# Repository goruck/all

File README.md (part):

*NEW - ALL now supports Raspberry Pi 3 running Raspbian Buster + PREEMPT-RT patched kernel 4.19.59-rt23-v7+.*

# What is Alexa Lambda Linux (ALL) Project?
* ALL is an end-to-end HW/SW reference design created to enable quick prototyping and realization of the control and monitoring of things using Amazon’s Alexa.
* ALL includes Amazon’s Alexa Skills Kit and Lambda running in the cloud as well as a local server based on real-time Linux running on the Raspberry Pi.
* ALL also includes machine learning capabilities at the edge. 
* A voice-controlled home security system was built from ALL as an early proof of concept.
* ALL was introduced in late 2015 at https://github.com/goruck/all.

# ALL System Block Diagram

# ALL Overview
Using voice to interface with devices and services around the home enables a rich and intuitive experience as shown by Amazon's huge successes with FireTV and Echo. However, with the exception of a few 3rd party point solutions such as WeMo, the voice user interface is generally not available in the home. One reason for this is the difficulty and unfamiliarity of the technologies required to enable voice control.

Alexa Lambda Linux (ALL) was developed to help accelerate this learning curve. ALL is a HW/SW reference design meant to enable quick prototyping and realization of the control and monitoring of things using Amazon's Alexa. A voice-controlled home security system was first built from the reference design as proof of concept which was later extended to support machine learning. 

The README below describes the system, the main components, its design, and implementation. It is expected that people will find it useful in creating voice user interfaces of their own using Alexa, Lambda, Linux, and the Raspberry Pi.

Feature | Benefit
------------ | -------------
Integrated with Lambda and ASK | Quick bring-up of new voice controls
Real-time Linux / user space app dev model | Low effort to control fast real-world events
Raspberry PI, open source, AWS services | Low cost and quick deployment
End to end SSL/TLS integration | Customer data security

# Table of Contents
1. [Requirements and System Architecture](https://github.com/goruck/all#requirements-and-system-architecture)
2. [Design and Implementation of the Main Components](https://github.com/goruck/all#design-and-implementation-of-the-components)
   1. [Alexa Intent Schema / Utterance database](https://github.com/goruck/all#alexa-intent-schema--utterance-database)
   2. [AWS Lambda function](https://github.com/goruck/all#aws-lambda-function)
   3. [Raspberry Pi Controller / Server](https://github.com/goruck/all#raspberry-pi-controller--server)
   4. [Keybus to GPIO Interface Unit](https://github.com/goruck/all#keybus-to-gpio-interface-unit)
3. [Machine Learning with ALL](https://github.com/goruck/all/blob/master/README.md#machine-learning-with-all)
   1. [Background Information](https://github.com/goruck/all/blob/master/README.md#background-information)
   2. [Problem Definition](https://github.com/goruck/all/blob/master/README.md#problem-definition)
   3. [Data Preparation](https://github.com/goruck/all/blob/master/README.md#data-preparation)
   4. [Data Analysis](https://github.com/goruck/all/blob/master/README.md#data-analysis)
   5. [Algorithm Evaluation](https://github.com/goruck/all/blob/master/README.md#algorithm-evaluation)
   6. [Implementation](https://github.com/goruck/all/blob/master/README.md#implementation)
   7. [Results](https://github.com/goruck/all/blob/master/README.md#results)
4. [Development and Test environment](https://github.com/goruck/all#development-and-test-environment)
5. [Overall Hardware Design and Considerations](https://github.com/goruck/all#overall-hardware-design-and-considerations)
6. [Bill of Materials and Service Cost Considerations](https://github.com/goruck/all#bill-of-materials-and-service-cost-considerations)
7. [Licensing](https://github.com/goruck/all/blob/master/README.md#licensing)
8. [Contact Information](https://github.com/goruck/all/blob/master/README.md#contact-information)
9. [Appendix](https://github.com/goruck/all#appendix)

# Requirements and System Architecture
Please see below the high-level requirements that the project had to meet.

* Low cost
* Extensible / reusable with low effort
* Secure
* Enable fast prototyping and development
* Include at least one real world application

Meeting these requirements would prove this project useful to a very wide variety of voice interface applications. In addition, implementing a non-trivial "real-world" application would show that the design is robust and capable. Hence the last requirement, which drove the implementation of a voice user interface on a standard home security system, the DSC Power832.

The system needs both cloud and (home-side) device components. Amazon's Alexa was selected as the cloud speech service and Amazon Web Services' Lambda was selected to handle the cloud side processing required to interface between Alexa and the home-side devices. Alexa is a good choice given that its already integrated with Lambda and has a variety of voice endpoints including Echo and FireTV and it costs nothing to develop voice applications via the [Alexa Skills Kit](https://developer.amazon.com/public/solutions/alexa/alexa-skills-kit). [Lambda](https://aws.amazon.com/lambda/) is ideal for quickly handling bursty processing loads, which is exactly what is needed to control things with voice. It also has a free tier under a certain amount of processing and above that its still very inexpensive. So, Alexa and Lambda are reasonable cloud choices given the requirements above.

The [Raspberry Pi 2](https://www.raspberrypi.org/blog/raspberry-pi-2-on-sale/) was designated as the platform to develop the home-side device components( All also supports the Raspberry Pi 3.) The platform has a powerful CPU, plenty RAM, a wide variety of physical interfaces, has support for many OSs, and is inexpensive. It is possible to use an even more inexpensive platform like [Arduino](https://www.arduino.cc/) but given its lower capabilities vis-a-vis the Raspberry PI this would limit the types of home-side applications that could be developed. For example, use of GNU/Linux is desirable in this project for extensibility and rapid development reasons. Arduino isn't really capable of running Linux but the Pi is. The downside of using the Pi plus a high-level OS like vanilla Linux is that the system cannot process quickly changing events (i.e., in "real-time"). On the other hand, the Arduino running bare metal code is a very capable real-time machine. To be as extensible as possible, the system needs to support the development of real-time voice controlled applications and without complex device side architectures like using an Arduino to handle the fast events connected to a Pi to handle the complex events. Such an architecture would be inconsistent with the project requirements. Therefore [real-time Linux](https://wiki.linuxfoundation.org/realtime/start) was chosen as the OS on the Pi. However, this comes with the downsides of using a non-standard kernel and real-time programming is less straightforward than standard application development in Linux userspace.

In the reference design, the Pi's GPIOs are the primary physical interface to the devices around the home that are enabled with a voice UI. This allows maximum interface flexibility, and with using real-time Linux, the GPIO interface runs fast. The reference design enables GPIO reads and writes with less than 60 us latency, vanilla Linux at best can do about 20 ms. Of course, all the other physical interfaces (SPI, I2C, etc.) on the Pi are accessible in the reference design though the normal Linux methods.

The requirements and the analysis above drove a system architecture with the following components.

* Alexa Skills developed using the Alexa Skills Kit
* An AWS Lambda function in Node.js to handle the intent triggers from Alexa and send it back responses from the home device 
* A home device built on Raspberry PI running real-time Linux with a server application developed in C running in userspace
* A hardware interface unit that handled the translation of the electrical signals between the Pi and the security system
* The DSC Power832 security system connected via its Keybus interface to the Pi's GPIOs via the interface unit.

Note that although the development of the architecture described above appears very waterfall-ish, the reality is that it took many iterations of architecture / design / test to arrive at the final system solution.

# Design and Implementation of the Components

## Alexa Skills
Creating Alexa Skills (which are essentially voice apps) is done by using the Alexa Skills Kit. An Amazon applications developer account is required to get access to the [Alexa Skills Kit (ASK)](https://developer.amazon.com/public/solutions/alexa/alexa-skills-kit), one can be created one at https://developer.amazon.com/appsandservices. There's a [getting started guide](https://developer.amazon.com/appsandservices/solutions/alexa/alexa-skills-kit/getting-started-guide) on the ASK site on how to create a new skill. The skill developed to control the alarm panel, named *panel*, used the example skill *color* as a starting point. Amazon makes the creation of a skill relatively easy but careful thinking through the voice interaction is required. The *panel* skill uses a mental model of attaching a voice command to every button on the alarm's keypad and an extra command to give the status of the system. The alarm system status is the state of the lights on the keypad (e.g., armed, bypass, etc). Four-digit code input is also supported, which is useful for a PIN. The Amazon skill development tool takes you through the following steps in creating the skill:

1. Skill Information - Invocation Name, Version, and Service Endpoint (the Lambda ARN in this project)
2. Interaction Model - Intent Schema, Custom Slot Types, and Sample Utterances
3. Test
4. Description
5. Publishing Information (the *panel* skill is not currently published)

The creation of the *panel* skill required inputting of an [Intent Schema](https://github.com/goruck/all/blob/master/ask/IntentSchema.txt) (which defines the voice interaction model), [sample utterances](https://github.com/goruck/all/blob/master/ask/SampleUtterances.txt), and [custom slot definitions](https://github.com/goruck/all/blob/master/ask/CustomSlotTypes.txt) which are essentially elaborations of the values of parameters used in the Intent Schema. The ASK service will generate a voice model from these inputs. 

The table below shows some of the mapping between example user requests and the sample utterance syntax used in the interaction model. 

Example User Request | Sample Utterance
---------------------|------------------
“Alexa, ask Panel for its status” | WhatsMyStatusIntent its status
“Alexa, ask Panel about its status” |WhatsMyStatusIntent its status
“Alexa, ask Panel for the status” | WhatsMyStatusIntent the status
“Alexa, ask Panel about the status” | WhatsMyStatusIntent the status
“Alexa, ask Panel for status” | WhatsMyStatusIntent status
“Alexa, ask Panel about status” | WhatsMyStatusIntent status
“Alexa, ask Panel for the status” | WhatsMyStatusIntent the status
“Alexa, ask Panel about the status” | WhatsMyStatusIntent the status
“Alexa, ask Panel what is the status” | WhatsMyStatusIntent what is the status
“Alexa, ask Panel what the status is” | WhatsMyStatusIntent what the status is
“Alexa, ask Panel what's the status” | WhatsMyStatusIntent what's the status
“Alexa, ask Panel to give me the status” | WhatsMyStatusIntent give me the status
“Alexa, ask Panel to give me its status” | WhatsMyStatusIntent give me its status
“Alexa, ask Panel to tell me the status” | WhatsMyStatusIntent tell me the status
“Alexa, ask Panel to tell me its status” | WhatsMyStatusIntent tell me its status
"Alexa, ask Panel for key pound" | MyNumIsIntent key {Keys}
"Alexa, ask Panel for button star" | MyNumIsIntent button {Keys}
"Alexa, ask Panel for key pad button 0" | MyNumIsIntent key pad button {Keys}
"Alexa, ask Panel for 8" | MyNumIsIntent {Keys}
"Alexa, ask Panel for pin 1234" | MyCodeIsIntent pin {Code}
"Alexa, ask Panel for code 5678" | MyCodeIsIntent code {Code}
"Alexa, ask Panel for 4545" | MyCodeIsIntent {Code}

The "LIST_OF_KEYS" slot enables the intent "MyNumIsIntent" to activate when Alexa hears the name of the buttons on the keypad defined by the slot. The intent "WhatsMyStatusIntent" activates when Alexa hears any of the status related utterances listed above. The intent "MyCodeIsIntent" activates when Alexa hears a 4-digit code. When the intents activate, they cause the service endpoint Lambda function to run and perform specific processing depending on the user intent.

The skill is invoked by saying to Alexa "ask panel" or "tell panel".

## AWS Lambda function
An Amazon Web Services account is needed to use Lambda, one can be created at at https://aws.amazon.com/. Like all AWS products, there is good [documentation](https://aws.amazon.com/lambda/) available on the AWS site that should be read to come up to speed, if not already familiar. Still it can be challenging to use the product, if unfamiliar with javascript, Node, and asynchronous programming which are all essential to using Lambda. Several books and articles including [*Sams Teach Yourself Node.js in 24 Hours*](http://smile.amazon.com/dp/0672335956) by Ornbo, [*JavaScript: The Good Parts*](http://smile.amazon.com/dp/0596517742) by Crockford, and [*Asynchronous programming and continuation-passing style in JavaScript*](http://www.2ality.com/2012/06/continuation-passing-style.html) by Rauschmayer can help to accelerate the learning curve. Lambda and Node.js is very well-suited to scale cloud side processing associated with applications like voice control, given that Lambda was designed to handle bursty applications and the non-blocking I/O benefits of Node.js.

The *color* skill and Lambda function example provided by ASK was used as a template to create the Lambda function for *panel*. Since the Lambda function needed to talk to a remote Raspberry Pi server, that functionality was added as well as modifying the logic and speech responses to suit the alarm application. The Lambda code uses the Node.js tls method to open, read, and write a TCP socket that connects to the remote Pi server which sends commands to and reads status from the panel. The tls method provides both authentication and encryption between the Lambda client and the Pi server. One of the biggest challenges in this development is the placement of the  callbacks that returned responses back to Alexa due to the async nature of Node.js. The rest of the Lambda function development was straightforward. 

The Lambda code is divided up into three parts, [all.js](https://github.com/goruck/all/blob/master/lambda/all.js) contains most of the functions required to process the speech intents from the Alexa service and interface to the local Pi in a client - server model. However, some Lambda code requires it to be released under the Amazon License which is in the [amzn](https://github.com/goruck/all/tree/master/lambda/amzn) directory. Lastly, the Lambda code common to all.js and the code in the amzn directory is in [shared.js](https://github.com/goruck/all/blob/master/lambda/shared.js).

## Raspberry Pi Controller / Server

### Real-time Linux
The Linux disto on the Pi is based on Debian 10 "Buster" with a custom built [Raspberry Pi Linux 4.19.y kernel](https://github.com/raspberrypi/linux/tree/rpi-4.19.y-rt) patched with rt-patch and configured as a fully preemptible kernel. The kernel was cross-compiled on a Linux host using the official [Raspberry Pi instructions](https://www.raspberrypi.org/documentation/linux/kernel/building.md) and [LeMaRiva's excellent HOWTO](https://lemariva.com/blog/2019/09/raspberry-pi-4b-preempt-rt-kernel-419y-performance-test) as guides. Also the wiki [real-time Linux](https://wiki.linuxfoundation.org/realtime/start) is an invaluable source of information on the rt-patch and how to write real-time code.

The latency of the patched kernel was measured using [Cyclictest](https://wiki.linuxfoundation.org/realtime/documentation/howto/tools/cyclictest/start) which showed a worse case latency of less than 135 us. So, that seemed to indicate that applications could reliably respond to events up to about 7.4 kHz which is sufficient for this application which needs to respond to events at a 1 KHz rate (see below).

The distribution of the latency on the patched kernel as measure by Cyclictest is shown below.

### Controller / Server Application
The application code on the Pi emulates a DSC keypad controller running in the Linux system's userspace. The application code in its entirety can be found [here](https://github.com/goruck/all/blob/master/rpi/kprw-server.c), this section captures important design considerations that are not obvious from the code itself or the comments therein.

The DSC system is closed and proprietary and besides the installation and programming information in the DSC manuals and what hackers have managed to figured out and posted on the Internet and GitHub, there isn't much information available about the protocol it uses to communicate with its keypads. Also, much of of what is on the Internet relies on using an IP interface bridge like this [one](http://www.eyezon.com/?page_id=176) from Eyezon. A bridge like this instead of the code on the Raspberry Pi could have been used in this project but that would have made the reference design much less generic (and much less fun to develop). A lot of useful information on how to hack the DSC system can be found in the [Arduino-Keybus](https://github.com/emcniece/Arduino-Keybus) GitHub repo, but this project uses an Arduino which was ruled out (see above) and it was read-only. Still, it is very educational. Although these sources helped, a lot of reverse engineering was required to figure out the protocol used on the DSC Keybus. The reverse engineering mainly consisted of using an early version of the application code to examine the bits sent from the panel to the keypads and the keypads to the panel in response to keypad button presses and other events, like motion and door / window openings and closings. It was determined that the first two bytes of each message indicates its type, followed by a variable number of data bits including error protection. For example a message with its first two bytes equal to 0x05 is telling the keypad to illuminate specific status LEDs, such as BYPASS, READY, etc and a message type equal to 0xFF indicates keypad to panel data is being sent. See the *decode()* function in the application code for details regarding the various message types and their contents.

The application code consists of three main parts:

* A thread called *panel_io()* that handles the bit-level processing needed to assemble messages from the keybus serial data
* A thread called *msg_io()* that handles the message-level output processing
* A server called *panserv()* running in the main thread that communicates with an external client for commands and status

The application code directly accesses the GPIO's registers for the fastest possible reads and writes. The direct access code is based on [this](http://elinux.org/RPi_GPIO_Code_Samples#Direct_register_access) information from the Embedded Linux Wiki at elinux.org. The function *setup_io()* in the application code sets up a memory regions to access the GPIOs. The information in the Broadcom BCM2835/6 ARM Peripherals document is very useful to understand how to safely access the Pi's processor peripherals. It is [here](http://elinux.org/RPi_Documentation) on the Embedded Linux Wiki site.

Inter-thread communication is handled safely via read and write FIFOs without any synchronization (e.g., using a mutext). Its not desirable to use conventional thread synchronization methods since they would block the *panel_io()* thread. There is no way (to my knowledge) to tell the panel not to send data on the keybus, so if *panel_io()* was blocked by another thread accessing a shared FIFO, the application code would drop messages. A good solution to this problem was found in the article [Creating a Thread Safe Producer Consumer Queue in C++ Without Using Locks](http://blogs.msmvps.com/vandooren/2007/01/05/creating-a-thread-safe-producer-consumer-queue-in-c-without-using-locks/) by Vandooren, which is what was implemented with a few modifications.

Running code under real-time Linux requires a few special considerations. Again, the [real-time Linux](https://rt.wiki.kernel.org/index.php/Main_Page) wiki was used extensively to guide the efforts in this regard. The excellent book [The Linux Programming Interface](http://man7.org/tlpi/) by Kerrisk also was very helpful to understand more deeply how the Linux kernel schedules tasks. There are three things needed to be set by a task in order to provide deterministic real time behavior:

1. Setting a real time scheduling policy and priority by use of the *sched_setscheduler()* system call and its pthread cousins. Note that *panel_io()*, *message_io()*, and *main()* were all given the same scheduling policy (SCHED_FIFO) but *panel_io()* has a higher priority than *message_io()* and *main()*. This was done to ensure that the bit-level processing would have enough time to complete. 
2. Locking memory so that page faults caused by virtual memory will not undermine deterministic behavior. This is done with the *mlockall()* system call. 
3. Pre-faulting the stack, so that a future stack fault will not undermine deterministic behavior. This is done by simply accessing each element of the program's stack by use of the *memset()* system call. 

Extensive use of the *clock_nanosleep()* function from librt is used in the code. For example, its use is shown in the *panel_io()* thread where it awakens the thread every INTERVAL (10 us) to read and write to the GPIOs driving the keybus clock and data lines (via the interface unit). The thread contains logic to detect the start of word marker, to detect high and low clock periods, and to control precisely when the GPIOs are read and written. The below taken from *panel_io()* causes the thread to wait for valid data before reading the GPIO.

```c
t.tv_nsec += KSAMPLE_OFFSET;
tnorm(&t);
clock_nanosleep(CLOCK_MONOTONIC, TIMER_ABSTIME, &t, NULL); // wait KSAMPLE_OFFSET for valid data
wordkr_temp = (GET_GPIO(PI_DATA_IN) == PI_DATA_HI) ? '0' : '1'; // invert
```

Even though the *panel_io()* is given higher priority than the other two threads, other critical threads in the Linux kernel must have higher still priority for the overall system to function. Therefore it is possible that a higher priority kernel task could preempt *panel_io()* and cause it to drop bits. The real-time Linux wiki suggests this solution:

*"In general, I/O is dangerous to keep in an RT code path. This is due to the nature of most filesystems and the fact that I/O devices will have to abide to the laws of physics (mechanical movement, voltage adjustments, <whatever an I/O device does to retrieve the magic bits from cold storage>). For this reason, if you have to access I/O in an RT-application, make sure to wrap it securely in a dedicated thread running on a disjoint CPU from the RT-application."* 

Based on this, the *panel_io()* thread was locked to its own CPU and the other threads are locked to the other three CPUs (its really great to have four CPUs at one's disposal). The application code sets the thread CPU affinity as shown below. 

```c
// CPU(s) for main, predict and message i/o threads
  CPU_ZERO(&cpuset_mio);
  CPU_SET(1, &cpuset_mio);
  CPU_SET(2, &cpuset_mio);
  CPU_SET(3, &cpuset_mio);
  CPU_ZERO(&cpuset_main);
  CPU_SET(1, &cpuset_main);
  CPU_SET(2, &cpuset_main);
  CPU_SET(3, &cpuset_main);
  // CPU(s) for panel i/o thread
  CPU_ZERO(&cpuset_pio);
  CPU_SET(0, &cpuset_pio);
```

With the threads pinning to the CPUs in this way and with the priority of *panel_io()* being greater than the other two threads in the application code (but not greater than the kernel's critical threads), the system exhibits robust real-time performance.

The server uses openSSL for authentication and encryption. For development and test purposes self-signed certificates are used. The cert and key pairs are generated with the following commands.

```bash
# Step 1. Generate ca private key
$ openssl genrsa -out /home/pi/certs/ca/ca.key 4096
# Step 2. Create self-signed ca cert, COMMON_NAME="My CA"
$ openssl req -new -x509 -days 365 -key /home/pi/certs/ca/ca.key -out /home/pi/certs/ca/ca.crt -sha256
# 
# Step 3. Create client private key
$ openssl genrsa -out /home/pi/certs/client/client.key 2048
# Step 4. Create client cert signing request, COMMON_NAME="Client 1"
$ openssl req -new -key /home/pi/certs/client/client.key -out /home/pi/certs/client/client.csr -sha256
# Step 5. Create signed client cert
$ openssl x509 -req -days 365 -in /home/pi/certs/client/client.csr -CA /home/pi/certs/ca/ca.crt -CAkey /home/pi/certs/ca/ca.key -set_serial 01 \
-out /home/pi/certs/client/client.crt -sha256
# 
# Step 6. Create server private key
$ openssl genrsa -out /home/pi/certs/server/server.key 2048
# Step 7. Create server cert signing request, COMMON_NAME="localhost"
$ openssl req -new -key /home/pi/certs/server/server.key -out /home/pi/certs/server/server.csr -sha256
# Step 8. Create signed server cert, where "key.ext" contains "subjectAltName = IP:xxx.xxx.xxx.xxx"
$ openssl x509 -req -days 365 -in /home/pi/certs/server/server.csr -CA /home/pi/certs/ca/ca.crt -CAkey /home/pi/certs/ca/ca.key -set_serial 02 \
-out /home/pi/certs/server/server.crt -sha256 -extfile /home/pi/certs/server/key.ext
# 
# Step 9. Copy client key pair and CA certificate to Lambda
$ cp /home/pi/certs/client/client.crt /home/pi/all/lambda
$ cp /home/pi/certs/client/client.key /home/pi/all/lambda
$ cp /home/pi/certs/ca/ca.crt /home/pi/all/lambda
```

Note: replace the X's in key.ext with the IP address or hostname of your server.

Production code should use certificates signed by a real CA. The server also uses TCP Wrapper daemon for secure access. TCP Wrapper uses the *hosts_ctl()* system call from libwrap library to limit client access via the rules defined in /etc/host.deny and /etc/host.allow files. The rules are set so that only clients with local IP addresses and AWS IP addresses are allowed access to the server.

The application code needs to be compiled with the relevant libraries and executed with su privileges, per the following.

```bash
# Install libs if needed.
$ sudo apt install libwrap0-dev libssl-dev
# Compile kprw-server.c.
# To enable R logging, add -DRLOG=\"/home/pi/all/R/rlog.txt\" (change path as required).
# To output status messages to stdout, add -DVERBOSE.
# To run a real-time safe test at start of program, add -DTESTRT.
$ gcc -Wall -o kprw-server kprw-server.c -lrt -lpthread -lwrap -lssl -lcrypto
# Start program.
# PORTNUM=69840 # TCP port number for the server to use (change as required).
$ sudo ./kprw-server $PORTNUM
```

### Startup
The Raspberry Pi is used here as an embedded system so it needs to come up automatically after power on, including after a possible loss of power. The application code defines the GPIOs as follows:

```c
// GPIO pin mapping.
#define PI_CLOCK_IN	(13) // BRCM GPIO13 / PI J8 Pin 33
#define PI_DATA_IN	(5)  // BRCM GPIO05 / PI J8 Pin 29
#define PI_DATA_OUT	(16) // BRCM GPIO16 / PI J8 Pin 36
``` 

These GPIOs need to be in a safe state after power on and boot up. Per the Broadcom BCM2835/6 ARM Peripherals document, these GPIOs are configured as inputs at reset and the kernel doesn't change that during boot, so they won't cause any the keybus serial data line to be pulled down before the application code initializes them. The BRCM GPIO16 was selected for the active high signal that drives the keybus data line since that GPIO has the option of being driven low from an external pull down. Other GPIOs have optional pull-ups. Even though the pull resistors are disabled by default, this removes the possibility of the keybus data line becoming active if software somehow enabled the pull resistor by mistake.

A known problem of the Raspbian Preempt-RT patches is that the IRQ/39-dwc_otg process can use a lot the CPU (~30%) which is caused by servicing the USB irq. Although this should not affect the real-time performance of this application given the thread priority settings, the USB ports can be disabled if they are not being. Since the RPi3's wifi chip is connected via SDIO to the processor and nothing else was needed to be connected to the USB ports they are disabled on startup in this configuration to improve the responsiveness of the system. This is done by [power-off-usb.sh](./scripts/power-off-usb.sh) script which is run by /etc/rc.local at startup. 

The kprw-server application is run as a Linux service enabled to run at boot time. See [kprw-server.service](./rpi/kprw-server.service).

## Keybus to GPIO Interface Unit

### Keybus Electrical and Timing Characteristics
The keybus is a DSC proprietary serial bus that runs from the panel to the sensors and controller keypads in the house. This bus needs to understood from an electrical, timing, and protocol point of view (see above) before the Pi can be interfaced to the panel. There isn't a lot of information on the keybus other than what's in the DSC installation manual and miscellaneous info on the Internet posted by hackers. Essentially, this is a two wire bus with clock and data, plus ground and the supply from the panel. The supply is 12 V (nominal) and the clock and data transition between zero volts and the supply voltage level (i.e., 0 to 12 V nominally but could be a bit more or less (~ +/-10%) depending on the specific panel). The large voltage swings make sense given that it provides good noise immunity against interference picked up from long runs of the bus through the house. The DSC manual states that the bus supply can source a max of 550 mA. The sum of the current from all the devices presently on the bus was about 400 mA. This meant that the interface unit could draw no more than 150 mA.

An oscilloscope was used to reverse engineer the protocol. Some screen-shots and analysis from them are below.

This shows an entire word with the start of new word marker, which is the clock being held high for a relatively long time. The clock rate when active is 1 KHz. The messages between the panel and keypads are of variable length. The typical message from the panel to the keypads is 43 bits (43 ms in duration) and the start of the new word clock marker is about 15 ms. Thus, a typical message time including start of new marker is about 58 ms. Messages can be up to 62 bits long but they are not frequent. 

This shows a closer view of the clock and data, with data being sent between the panel and keypad and vice-versa. Data from the panel to the keypads transitions on the rising edge of the clock and becomes valid about 120 us later. Data from the keypads to the panel transitions at falling edge of the clock is likely registered in the panel on the next rising edge of the clock. The keypad data needs to be held for at least 25 us after the rising edge of the clock for it to be properly registered. Timers in the Pi's application code must adhere to these values for reliable data transfers to happen. The spikes at 2.5 and 4.5 ms are most likely due to the pull-up resistor on the data line in the panel causing it to be pulled high before the driver on the keypad has a chance to pull it low, which happens when the keypad sends a 0 bit to the panel.

From this data, it is clear that the panel's data line is bidirectional (with direction switched by clock level) and pulled up internally when configured as an input. The strength of the pull-up resister needs to be known in order to design the interface circuit correctly and via experimentation it was determined to be approximately 5 KΩ.

Note that a means to prevent or mitigate keybus data corruption needs to be implemented since ALL may try to write to the panel at the same time as a keypad. This is done in the rpi code by checking for very short words sent by the panel on the keybus. The panel outputs short words (usually 9-bits) which are ignored as invalid since these short words are usually associated with the simultaneous transfer of keypad data to the panel (recall from above the keybus is bidirectional and bits are transferred on the rising and falling edge of the clock). This keypad data is sent in response to a panel keypad query command that was sent previously. These commands include those messages starting with 0x051, 0x0593, 0x11 and possibly others.

### Raspberry Pi GPIO Electrical Characteristics
Data on the electrical characteristics of the Pi's GPIOs is also required to design the interface. There is not really the right level of detail available from the Raspberry Pi standard information. But there is excellent information on the Mosaic Industries' website [here](http://www.mosaic-industries.com/embedded-systems/microcontroller-projects/raspberry-pi/gpio-pin-electrical-specifications). This information is super helpful and detailed. Some of the key points from the article are below. 

* These are 3.3 volt logic pins. A voltage near 3.3 V is interpreted as a logic one while a voltage near zero volts is a logic zero. A GPIO pin should never be connected to a voltage source greater than 3.3V or less than 0V, as prompt damage to the chip may occur as the input pin substrate diodes  conduct. There may be times when you may need to connect them to out ­of ­range voltages – in those cases the input pin current must be limited by an external resistor to a value that prevents harm to the chip. I recommend that you never source or sink more than 0.5 mA into an input pin
* To prevent excessive power dissipation in the chip, you should not source/sink more current from the pin than its programmed limit. So, if you have set the current capability to 2 mA, do not draw more than 2 mA from the pin
* Never demand that any output pin source or sink more than 16 mA
* Current sourced by the outputs is drawn from the 3.3 V supply, which can supply only 50 mA maximum. Consequently, the maximum you can source from all the GPIO outputs simultaneously is less than 50 mA. You may be able to draw transient currents beyond that limit as they are drawn from the bypass capacitors on the 3.3 V rail, but don't push the envelope! There isn't a similar limitation on sink current. You can sink up to 16 mA each into any number of GPIO pins simultaneously. However, transient sink currents do make demands on the board's bypass capacitors, so you may get into trouble if all outputs switch their maximum current synchronously
* Do not drive capacitive loads. Do not place a capacitive load directly across the pin. Limit current into any capacitive load to a maximum transient current of 16 mA. For example, if you use a low pass filter on an output pin, you must provide a series resistance of at least 3.3V/16mA = 200 Ω

### Interface Circuit Design
Its desirable to electrically isolate the panel and Pi to prevent ground loops and optoisolators are an obvious choice. But they do consume a fair amount of current and the keybus data and clock lines cannot supply enough to directly drive them. Therefore, the keybus clock and data lines have buffers (CD4050) between them and the optoisolators. Out of an abundance of caution, buffers (74HC126) were also added between the clock and data optoisolators and the Pi's GPIOs, but they are not really needed since the Pi's GPIOs come out of reset being able to supply or sink 8 mA while the interface circuit only needs a 2 mA supply. The '126 buffers were removed in the final design. A high Current Transfer Ratio (CTR) optoisolator configured to drive a FET with logic-level gate voltage threshold was used to pull down the data line with sufficient strength. The other optoisolators are high CTR as well to minimize current draw from the panel. The interface schematic is shown below.

# Machine Learning with ALL
Adding machine learning (ML) capabilities to ALL was mainly motivated by a desire to use Alexa to help train a ML algorithm in an intuitive and low-friction manner by employing voice to ground truth (or 'tag') observations. Also since ALL uses a home security system as a proof-of-concept, ML seemed to be a natural fit given the amount of data captured by the security system's sensors. Door, window, and motion data is continually captured which reflects the movement of people into and around the house. Of course, normally this data is used for security monitoring purposes but here the goal of adding machine learning to ALL was to use this data to reliably predict patterns of people movement around the house that would trigger appropriate actions automatically. Using ML as described below can also be used to become familiar with the topic itself since the application is fairly straightforward and tractable.

Its important to note that simple rule based algorithms can be employed instead of ML to trigger actions based on the sensor data. However, this is really only feasible for the most basic patterns of movement around the house. 

## Background Information
### Training ML Models *(This section adapted from [here](http://docs.aws.amazon.com/machine-learning/latest/dg/training-ml-models.html))*
The process of training an ML model involves providing an ML algorithm (that is, the learning algorithm) with training data to learn from. The term ML model refers to the model artifact that is created by the training process.

The training data must contain the correct answer, which is known as a response. The learning algorithm finds patterns in the training data that map the input data predictors to the response (the answer that you want to predict), and it outputs an ML model that captures these patterns.

The ML model is used to get predictions on new data for which a response is not known.

### Steps to build and train a predictive ML model
1. Define the problem that predictive ML model will solve for.
2. Prepare the data that will be used to train the ML model.
3. Analyze the training data to help guide ML algo selection. 
4. Select a suitable algorithm for the ML model. 
5. Evaluate and optimize the ML model’s predictive accuracy.
6. Use the ML model to generate predictions.

### R
The popular open-source software R was selected as the main ML tool and was intended to be used for both modeling and embedded real-time purposes which helps to accelerate development by reusing code. The excellent book [An Introduction to Statistical Learning](http://smile.amazon.com/dp/B01IBM7790) was extensively used as both a learning guide to ML and to R.

The R software package was downloaded from [The R Project for Statistical Computing](https://www.r-project.org/) website and compiled on the Raspberry Pi since there are no recent pre-compiled packages available for Raspbian Wheezy. The following steps are required to install R on the Pi.

```bash
$ cd ~
$ wget http://cran.rstudio.com/src/base/R-3/R-3.6.1.tar.gz
$ mkdir R_HOME
$ mv R-3.6.1.tar.gz R_HOME/
$ cd R_HOME/
$ tar zxvf R-3.6.1.tar.gz
$ cd R-3.6.1/
$ sudo apt-get install gfortran libreadline-dev libx11-dev libxt-dev \
libbz2-dev liblzma-dev libpcre3-dev libcurl4-gnutls-dev
$ ./configure
$ make
$ sudo make install
```

Note that this installs R version 3.6.1 which is the latest compatible version for Raspbian Buster.

## Problem Definition
It is important to first understand and clearly describe the problem that is being solved including how training will be done. Here, the problem is to accurately predict a person's movement into and through the house using the security system's motion and door sensors (the window sensors are ignored for the present) and to take action on that prediction.

The proof of concept system is installed in a two story house with a detached playroom / garage in the rear, accessible via a short walk through the backyard. The relevant sensors are as follows.

Zone | Sensor
-----|-------
1  | Front Door
16 | Family Room Slider (rear house exit)
27 | Front Motion
28 | Hall Motion (first floor)
29 | Upstairs Motion (second floor hall)
30 | Playroom Motion (in detached unit behind house)
32 | Playroom Door

Thus, as a person traversed through the zones listed above the problem is to predict the path taken, speed of travel and direction of travel. An example path could be a person arriving home, entering through the front door, walking into the family room via the first floor hall, exiting the house through the rear family room slider door and into the playroom. Patterns can also be time of day dependent (example being a person arriving home around the same time in the evening and following the above path). These sensors and the time of day will be used to fit the model and as inputs to the model to make predictions. 

A related problem is how to train the model in the most intuitive and easiest manner possible for the user. A good solution is tagging the patterns as the occur with voice via Alexa. For example, if a person walked the above pattern at 7:00 PM, she would tell Alexa that ("Alexa, I'm home") which would trigger a sequence of events to capture an observation and update the ML model.

A typical use case is shown in the figure below, where a person arrives home at a specific time and turns on the TV. The person would tell Alexa this happened and after a fashion the TV would automatically be turned on (and perhaps Fire TV would stream a favorite show) when this pattern is detected.

## Data Preparation
Considerable thought was put into understanding the sensor information required to develop the ML model. The native output from the sensors is binary - the sensor is either activated by movement or its not due to lack of movement. For security monitoring purposes this is normally sufficient but this binary information needs to be transformed into a continuous time series to be useful as inputs to the model described above. This transformation is accomplished by applying a time-stamp to every activation or deactivation of a sensor, which is called the 'absolute' time of an observation. The timestamped sensor data is not used directly to build / update the ML model or predict a pattern. Instead a version of the timestamped data is used which is the last activation / deactivation time of a sensor relative to the current observation time. The relative data is required to ensure that the training data used to build the model are consistent with new data used for prediction. An example transformation for a four sensor zone example is shown in the figure below.

Relative activation and deactivation times for each sensor along with the time and date, sample time, and the response ground truth for a specific pattern form a training predictor vector based on a single observation. A collection of these vectors form a dataset from which a model can be generated. Similarly, a test vector is formed from new sensor data (without the ground truth) that is used by the model to make predictions. 

An example training predictor vector is shown below, where 'clock' is the time and date of the observation, 'sample' is a time-stamp value in seconds (derived from Linux system time of the server), 'zaNN' is the sensor activation time in seconds relative to the time-stamp, 'zdNN' is the sensor deactivation time in seconds relative to the time-stamp, and 'patternNN' is the response ground truth for a specific pattern for the given observation.

| clock                    | sample  | za1    | za2      | za3      | za4      | za5      | za6      | za7      | za8      | za9      | za10     | za11     | za12     | za13     | za14     | za15     | za16 | za17     | za18     | za19     | za20     | za21     | za22     | za23     | za24     | za25  | za26  | za27 | za28 | za29 | za30 | za31     | za32 | zd1    | zd2      | zd3      | zd4      | zd5      | zd6      | zd7      | zd8      | zd9      | zd10     | zd11     | zd12     | zd13     | zd14     | zd15     | zd16 | zd17     | zd18     | zd19     | zd20     | zd21     | zd22     | zd23     | zd24     | zd25     | zd26     | zd27 | zd28 | zd29 | zd30 | zd31     | zd32 | pattern1 | pattern2 | pattern3 | pattern4 | pattern5 | pattern6 | pattern7 | pattern8 | pattern9 | pattern10 |
|--------------------------|---------|--------|----------|----------|----------|----------|----------|----------|----------|----------|----------|----------|----------|----------|----------|----------|------|----------|----------|----------|----------|----------|----------|----------|----------|-------|-------|------|------|------|------|----------|------|--------|----------|----------|----------|----------|----------|----------|----------|----------|----------|----------|----------|----------|----------|----------|------|----------|----------|----------|----------|----------|----------|----------|----------|----------|----------|------|------|------|------|----------|------|----------|----------|----------|----------|----------|----------|----------|----------|----------|-----------|
| 2016-07-30T21:54:37.950Z | 4134765 | -14172 | -4134765 | -4134765 | -4134765 | -4134765 | -4134765 | -4134765 | -4134765 | -4134765 | -4134765 | -4134765 | -4134765 | -4134765 | -4134765 | -4134765 | -51  | -4134765 | -4134765 | -4134765 | -4134765 | -4134765 | -4134765 | -4134765 | -4134765 | -8066 | -6541 | -31  | -37  | -12  | -70  | -4134765 | -72  | -14164 | -4134765 | -4134765 | -4134765 | -4134765 | -4134765 | -4134765 | -4134765 | -4134765 | -4134765 | -4134765 | -4134765 | -4134765 | -4134765 | -4134765 | -47  | -4134765 | -4134765 | -4134765 | -4134765 | -4134765 | -4134765 | -4134765 | -4134765 | -4134765 | -4134765 | -30  | -32  | -6   | -68  | -4134765 | -69  | NA       | NA       | NA       | NA       | NA       | NA       | NA       | TRUE     | NA       | NA        |

## Data Analysis
Once it was understood how to form a relevant sensor dataset for the model the next step was to discover and expose the structure in the dataset. Using the above transformations, a dataset of about 300 observations was collected and visualized in scatterplots using R's graphical capabilities. The R code that generated these plots can be found [here](https://github.com/goruck/all/blob/master/R/genScatterPlots.R) and the observation dataset can be found [here](https://github.com/goruck/all/blob/master/R/panelSimpledb.csv).

Eight unique patterns were used to generate the observations. Each pattern corresponds to a path, direction, and speed of a person walking though the house and the approximate hour of the day this pattern occurred. The training was done by walking the pattern a few times and then invoking an Alexa skill that aquired the sensor data. The patterns and the zones they activate are summarized in the table below.

Pattern Number | Path | z1 | z16 | z27 | z28 | z29 | z30 | z32 | clock
-------|---------|----|-----|-----|-----|-----|-----|-----|-------
0 | virtual pattern that indicates no path has been classified | N | N | N | N | N | N | N | N
1 | from front door into playroom in the evening | Y | Y | Y | Y | N | Y | Y | ~7:00PM
2 | from outside into playroom | N | N | N | N | N | Y | Y | N
3 | from family room into playroom | N | Y | N | N | N | Y | Y | N
4 | slow walk from kid's rooms to playroom | N | Y | Y | Y | Y | Y | Y | N
5 | fast walk from kid's rooms to playroom | N | Y | Y | Y | Y | Y | Y | N
6 | from master bedroom to kitchen in the early morning via living room | N | N | Y | N | Y | N | N | ~4:00AM
7 | reserved | N | N | N | N | N | N | N | N
8 | from playroom to kid's rooms | N | Y | Y | Y | Y | Y | Y | N
9 | reserved | N | N | N | N | N | N | N | N
10 | reserved | N | N | N | N | N | N | N | N

An example R generated scatterplot for the response 'pattern6' (walking from the upstairs to the kitchen via the front hall in the early morning) is shown in the figure below. Note that a temporal filter is always applied to the data that limits sensor times to 120 seconds which is about the maximum time it takes a person to walk a particular path through the house. Sensor data outside this window is not relevant. 

Another example scatterplot for 'pattern4' (slow walk from the kid's rooms to the playroom via the front hallway) is shown in the figure below.

The axis for each plot is time in seconds from 0 to -120 with the exception of clock which is in hours from 0 to 23. The red dots are samples where the response is true, the black dots are where the response is false. From the scatterplots, the following can be determined.

* The data is not linearly separable between the true and false responses, so a non-linear model will be required.
* The true responses tend to be tightly clustered and surrounded by false responses, perhaps indicating a higher order non-linear model will be needed.
* The sensor predictors tend to be related by the fact they are offset in time from each other. The offset forms the basic pattern that needs to be classified.
* The data appears relatively unstructured in that there are not well defined regions of true and false responses (the 'decision boundary'). 
* Some patterns will have predictors that are not relevant since in general a path does not involve every sensor.
* An ensemble of two models may be required, one with clock as a predictor and one without it to handle observations taken around a particular time and those at random times.
* The data will need to be normalized given that the clock and sensor activation times are in different units. 

## Algorithm Evaluation
Now that the structure in the dataset is understood candidate model algorithms were evaluated using an R-based test harness.

Given the relatively unstructured decision boundary and non-linear nature of the dataset, the K-Nearest Neighbors (KNN), Random Forests and Support Vector Machine (SVM) algorithms are reasonable choices given that they are well-understood, non-parametric methods and have high flexibility (note that non-parametric models generally have the disadvantage of growing more complex as the number of observations increases). See [An Introduction to Statistical Learning](http://smile.amazon.com/dp/B01IBM7790) for details about the KNN, Random Forests, and SVM algorithms and their relative strengths and weaknesses. In the interest of time, only KNN and SVM approaches were evaluated and overall SVM seemed to offer better over performance (at the expense of more complexity) for the sensor dataset and so therefore was selected. The dataset provides a set of training observations that can be used to build a SVM-based multiple-class classifier. SVM uses the one-versus-one for multiple classification. More information about using SVMs in R can be found [here](https://cran.r-project.org/web/packages/e1071/vignettes/svmdoc.pdf).

An SVM with a radial kernel was selected given the non-linear class boundaries of the datasets. Cross-validation was used to select the best values of the parameters *gamma* and *cost* associated with the model. The R script to generate and test the SVM model can be found [here](https://github.com/goruck/all/blob/master/R/genSvmTest.R) with the dataset [here](https://github.com/goruck/all/blob/master/R/panelSimpledb.csv). The script generates confusion matrices for training and validation data.

The confusion matrix for the training data shown below. The numbers in the row and column headers represent the pattern number classified with 0 being the null case (i.e., no pattern was classified). Note that only patterns 1 through 8 were used and with clock as a factor in these examples. This data indicates that model is trained very well except for pattern 8. This is most likely because pattern does not yet have enough training samples in the current dataset. 

```text
> ### training error of optimal svm model with clock as a predictor
> svmPred = predict(svmOpt, trainData, probability = TRUE)
> table(predict = svmPred, truth = trainLabels)
       truth
predict   0   1   2   3   4   5   6   8
      0 125   0   0   0   0   0   0   5
      1   0   5   0   0   0   0   0   0
      2   0   0  18   0   0   0   0   0
      3   0   0   0  10   0   0   0   0
      4   0   0   0   0  24   0   0   0
      5   0   0   0   0   0   6   0   0
      6   0   0   0   0   0   0  12   0
      8   0   0   0   0   0   0   0   0
```
The confusion matrix for the test data shown below where a number of false negatives are shown particularly for patterns 2, 3, 5, and 8. This could indicate that the model is over-fitted or, as in the case of pattern 8, patterns have insufficient training data. Patterns 2 and 3 also use relatively few factors which likely increases the prediction error. The model will need to be refined as the dataset grows with additional training observations and its prediction performance is evaluated over time. 

```text
> ### test error of optimal svm model with clock as a predictor
> svmPred = predict(svmOpt, testData, probability = TRUE)
> table(predict = svmPred, truth = testLabels)
       truth
predict  0  1  2  3  4  5  6  8
      0 51  0  4  2  0  2  0  3
      1  0  2  0  0  0  0  0  0
      2  0  0  2  0  0  0  0  0
      3  1  0  0  6  0  0  0  0
      4  0  0  0  0 10  0  0  0
      5  0  0  0  0  0  5  0  0
      6  0  0  0  0  0  0  4  0
      8  0  0  0  0  0  0  0  0
```

R's summary function can be used to obtain some information about the SVM fit, the output is shown below. It can be seen that there is a large number of support vectors which indicates a complex decision boundary. This is also evident from the scatterplots above. 

```text
> summary(svmOpt)

Call:
svm(formula = y ~ ., data = trainData, kernel = "radial", gamma = svmTuneOut$best.model$gamma, 
    cost = svmTuneOut$best.model$cost, decision.values = FALSE, probability = TRUE, 
    scale = TRUE)

Parameters:
    SVM-Type: C-classification 
  SVM-Kernel: radial 
        cost: 100 
       gamma: 1 

Number of Support Vectors:  149

 ( 94 16 2 13 4 9 5 6 )

Number of Classes:  8 

Levels: 
 0 1 2 3 4 5 6 8
```

## Implementation
Now that the algorithm was selected, the next step was to implement the real-time prediction of patterns, develop an Alexa skill that performs voice tagging of training observations, and develop a method to periodically re-fit the SVM with new training data.

### Real-time Prediction and Action
A new thread called *predict()* was added to the [Raspberry Pi real-time software](https://github.com/goruck/all/blob/master/rpi/kprw-server.c) which runs periodically and sends sensor data to an R script via the *popen()* Linux system command to make a prediction. The prediction R script is found [here](https://github.com/goruck/all/blob/master/R/predsvm2.R). The thread reads the prediction from R, applies some confidence checking rules and does something if a true prediction is determined. Currently, various WeMo light switches in the house are controlled by the thread in response to predictions in a hardcoded manner but at some point a more flexible and extensible mapping of predictions to actions will be implemented (perhaps by use of another Alexa skill). The WeMo devices are controlled by a bash script called by a *system()* Linux system command in the thread. The WeMo bash script can be found [here](./scripts/wemo.sh). At some point the capability to automatically take action on a prediction will be added. This can be done by including the state of a WeMo switch as a factor in the model. Obviously, any device around the home that can be monitored and controlled through the LAN or Internet can be used as well.

Two models are used in the prediction R script, one that uses the clock as a prediction and one that does not. If both models predict the same pattern, the higher probability prediction is selected (in the case of both models making the same non-null prediction, a higher probability pattern from the model using clock as a predictor is likely a timed pattern that uses the clock). If one model has not identified any pattern and the other has, then the non-null case is selected.

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
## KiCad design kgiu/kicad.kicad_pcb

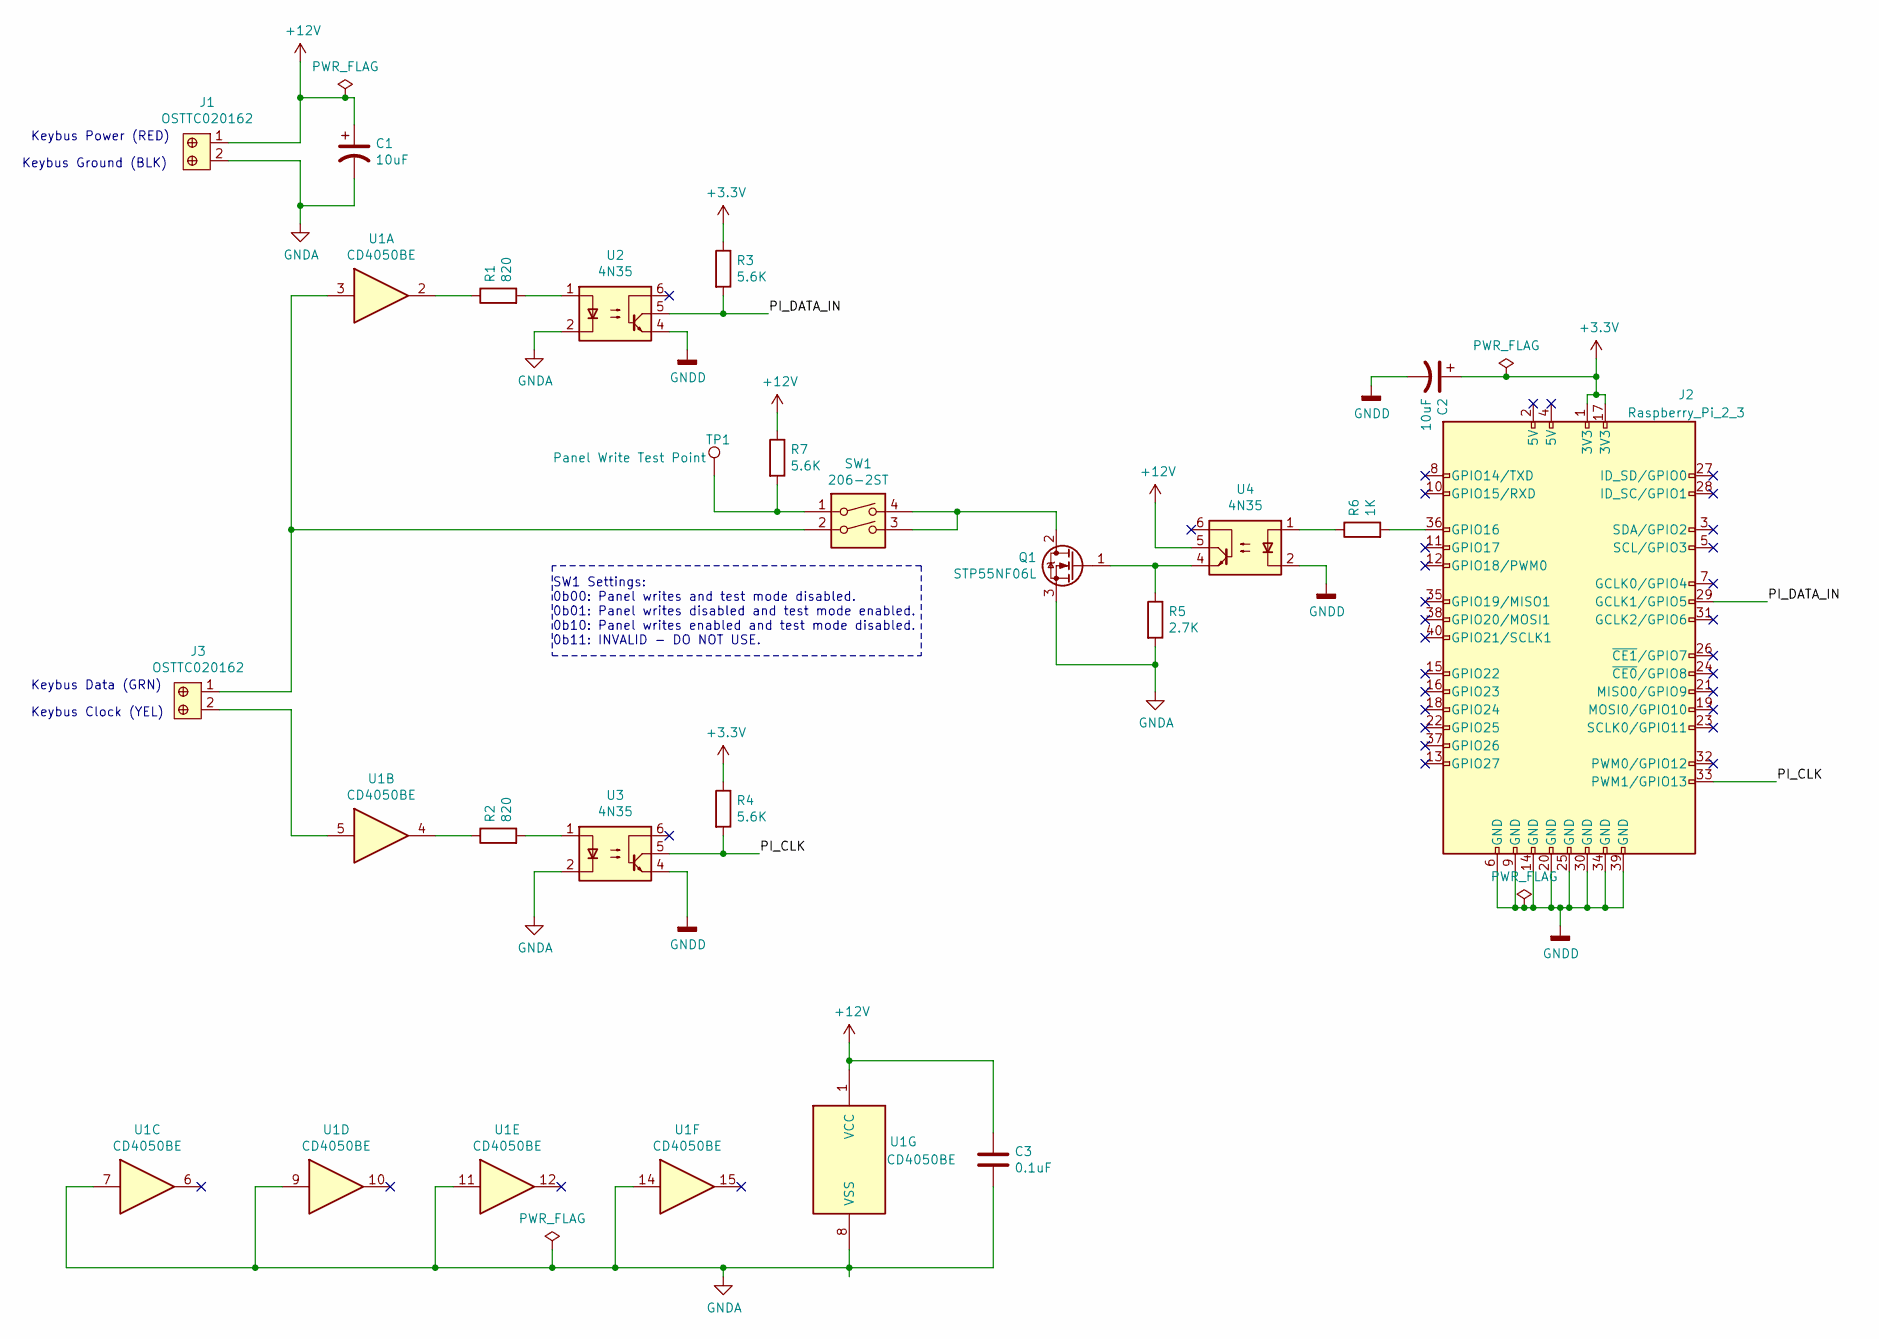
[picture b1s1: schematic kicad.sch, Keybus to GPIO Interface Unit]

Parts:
C1, C2: 10uF; CP_Axial_L11.0mm_D6.0mm_P18.00mm_Horizontal; MPN 106TTA035MSD
C3: 0.1uF; C_Disc_D3.0mm_W1.6mm_P2.50mm; MPN K104K15X7RF5TL2; Digi-Key-PN BC1084CT-ND
J1, J3: OSTTC020162; Term_Block_1x2_P5mm; MPN OSTTC020162; Digi-Key_PN ED2600-ND
J2: Raspberry_Pi_2_3; PinSocket_2x20_P2.54mm_Vertical; Digi-Key-PN S6104-ND
Q1: STP55NF06L; TO-220-3_Horizontal_TabDown; Digi-Key-PN 497-6742-5-ND
R1, R2: 820; R_Axial_DIN0207_L6.3mm_D2.5mm_P10.16mm_Horizontal; Digi-Key-PN CF14JT820RCT-ND
R3, R4, R7: 5.6K; R_Axial_DIN0207_L6.3mm_D2.5mm_P10.16mm_Horizontal; Digi-Key-PN CF14JT5K60CT-ND
R5: 2.7K; R_Axial_DIN0207_L6.3mm_D2.5mm_P10.16mm_Horizontal; Digi-Key-PN CF14JT2K70CT-ND
R6: 1K; R_Axial_DIN0207_L6.3mm_D2.5mm_P10.16mm_Horizontal; Digi-Key-PN CF14JT1K00CT-ND
SW1: 206-2ST; SW_DIP_SPSTx02_Slide_9.78x7.26mm_W7.62mm_P2.54mm; MPN 206-2ST; Digi-Key-PN CT2062ST-ND
TP1: Panel Write Test Point; TestPoint_Pad_2.0x2.0mm
U1: CD4050BE; DIP-16_W7.62mm; MPN CD4050BE; Digi-Key-PN 296-2056-ND
U2, U3, U4: 4N35; DIP-6_W7.62mm; MPN 4N35; Digi-Key_PN 160-1304-5-ND

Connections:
+3V3: C2.1, J2.1 (3V3), J2.17 (3V3), R3.1, R4.1
+12V: C1.1, C3.1, J1.1, R7.1, U1.1 (VCC), U4.5
/PI_CLK: J2.33 (PWM1/GPIO13), R4.2, U3.5
/PI_DATA_IN: J2.29 (GCLK1/GPIO5), R3.2, U2.5
GNDA: C1.2, C3.2, J1.2, Q1.3 (S), R5.2, U1.7, U1.8 (VSS), U1.9, U1.11, U1.14, U2.2, U3.2
GNDD: C2.2, J2.6 (GND), J2.9 (GND), J2.14 (GND), J2.20 (GND), J2.25 (GND), J2.30 (GND), J2.34 (GND), J2.39 (GND), U2.4, U3.4, U4.2
unnamed: J2.36 (GPIO16), R6.2
unnamed: J3.1, SW1.2, U1.3
unnamed: J3.2, U1.5
unnamed: Q1.1 (G), R5.1, U4.4
unnamed: Q1.2 (D), SW1.3, SW1.4
unnamed: R1.1, U1.2
unnamed: R1.2, U2.1
unnamed: R2.1, U1.4
unnamed: R2.2, U3.1
unnamed: R6.1, U4.1
unnamed: R7.2, SW1.1, TP1.1

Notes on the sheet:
Keybus Power (RED)
Keybus Ground (BLK)
Keybus Clock (YEL)
Keybus Data (GRN)
SW1 Settings: 0b00: Panel writes and test mode disabled. 0b01: Panel writes disabled and test mode enabled. 0b10: Panel writes enabled and test mode disabled. 0b11: INVALID - DO NOT USE.

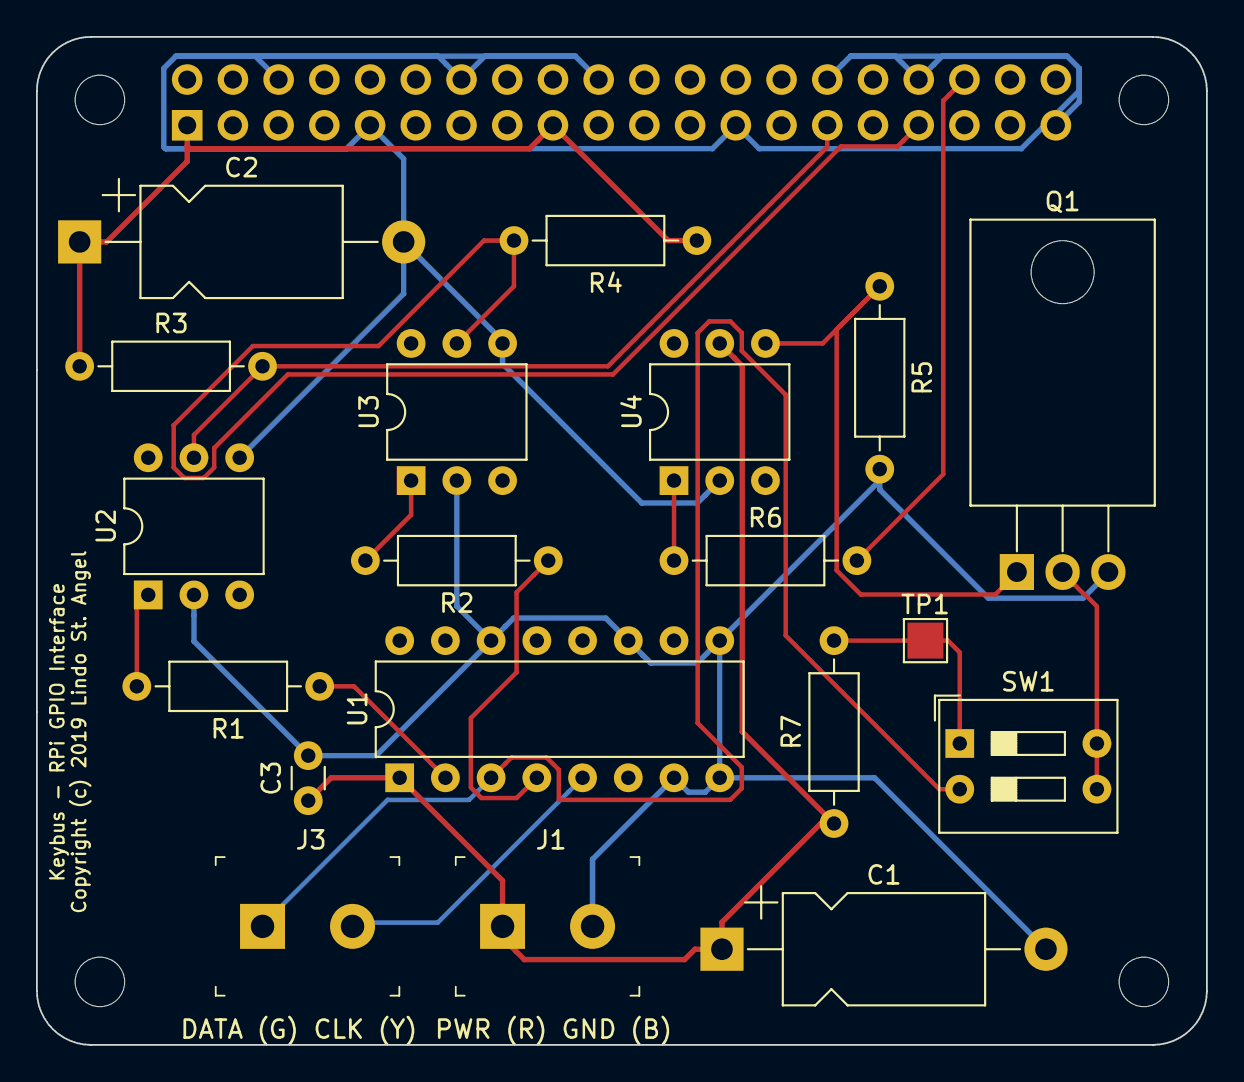
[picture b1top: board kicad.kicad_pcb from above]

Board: 2 copper layers, 65.0 x 56.0 mm, 20 parts (1 on the bottom side), 17 nets.

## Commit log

2015-12-07 modified README
2015-12-08 removed IP addr
2015-12-08 init commit
2015-12-10 added terminal screnshot
2015-12-10 added proto pics to readme.md
2015-12-10 added netbus schematic to readme
2015-12-13 removed doc/all-blockdia.odg and doc/all-overview.odp
2015-12-20 added CPU_SET for main
2015-12-20 added .gitignore
2015-12-20 changed PI_DATA_OUT to use GPIO16
2015-12-24 updated interface schematic in README.md
2015-12-24 init commit v1.1
2015-12-24 removed old netbus-gpio-if.jpeg sch
2015-12-27 Fixed AWS Lambda pricing info + misc typos.
2016-01-02 misc typo corrections
2016-01-03 added 4-digit code input support
2016-01-03 added 4-digit code input and error handling
2016-01-03 updated to reflect 4-digit code entry support
2016-01-09 added hardware design section to readme
2016-01-09 updated readme hardware design section
2016-01-09 updated readme; BOM costs and typos
2016-01-09 updated readme; typos and links
2016-01-17 mutual TLS auth enabled
2016-01-17 readme reflects that mutual TLS auth enabled
2016-01-17 updated openSSL commands to gen certs and key pairs
2016-01-23 host and port now read from file
2016-01-23 fixes for 5 digit server port number
2016-01-23 made server port number a command line arg
2016-01-23 changes to reflect server port num is passed to rpi application
2016-01-31 fixed typos
2016-01-31 updated tls method example in lambda section
2016-02-07 session now ends after any command; log intent name
2016-02-08 updated Alexa Intent Schema / Utterance database section
2016-02-09 enhanced welcome response; more detailed help
2016-02-21 check panel status before sending commands
2016-02-26 added checks to confirm commands took effect + misc cleanup
2016-02-26 mods to panserv to reflect more logical flow
2016-02-28 fixed zone numbering, now all labled 1 to 8
2016-02-28 added friendly name support
2016-02-28 inital commit
2016-02-28 updated lambda section to reflect latest code
2016-03-01 added stop and cancel intents
2016-03-06 fixed system ready falsing problem and cleaned up code
2016-03-06 cleaned up verifyArmCmd() logic
2016-03-12 updated to match latest code
2016-03-12 added utterences to improve recognition
2016-03-27 added zone activation and deactivation status
2016-03-27 moved fflush to right place
2016-05-12 integrated R
2016-05-12 test of branch
2016-05-12 first try at training
2016-05-16 support for ML voice tags
2016-05-16 support for machine learning
2016-05-17 modified predict thread to output entire R prediction
2016-05-17 modified output of pred to highlight its from R
2016-05-23 misc edits
2016-05-23 latest observation database
2016-05-23 first try at polly skill handler
2016-05-23 misc changes
2016-05-28 latest debug changes to polly
2016-05-28 latest debug changes
2016-05-28 latest database
2016-05-28 latest timestamp
2016-06-05 added page fault detection, general cleanup
2016-06-05 debug changes to polly
2016-06-05 misc cleanup
2016-06-05 using panelStatus to send commands + cleanup
2016-06-05 added polly and training support
2016-06-05 modified LiCENSE notice
2016-06-05 updated panel_io thread fault handling
2016-06-14 replaced modulus operator in fifos w/simpler code
2016-06-20 added time as a feature to the model
2016-06-20 added time as a feature to the ML model
2016-06-20 no longer using lubridate for date/time ops - too slow to load
2016-06-26 better error handling and optional data size limit code
2016-06-26 added R log file support
2016-07-02 added occupancy determination based on zone activity
2016-07-04 trainInSession() handles NA observations now
2016-07-04 predknn.R handles NA observations now
2016-07-04 tag server command name changed to sendJSON
2016-07-04 tag server command name chnaged to sendJSON; CONZONEUL now 10 s
2016-07-04 fixed sendJSON cmd string compare length
2016-07-06 changed database to panelSimpledb
2016-07-06 added support for 10 pattern matches
2016-07-06 training data processing per pattern; support for 10 patterns
2016-07-06 added support for 10 patterns
2016-07-11 added last prediction update
2016-07-11 added last prediction status and cleaned up prediction thread
2016-07-11 k = 1 test
2016-07-18 added svm model regeneration
2016-07-18 latest k changes to test perf
2016-07-18 initial rev of svm based prediction
2016-07-18 inital rev of svm model gen script
2016-07-18 misc changes to text to speech handleing
2016-07-18 changes for svm prediction
2016-07-24 fixed pattern to friendly name conversion
2016-07-24 changed to work with single svm model R script
2016-07-24 changed to use single svm model R script
2016-07-24 modified so that pred and prob are returned on 1 line
2016-07-24 modified so that probs are used with predictions
2016-07-30 changed rules in predict thread; removed misc debug; misc cleanup
2016-07-30 findPlacesNotReady now ignores motion sensors
2016-07-30 two svms are generated with and without clock as predictor
2016-07-30 uses 2 svm models, one with clock as predictor the other without
2016-07-31 added OccupancyIsIntent and PredIsIntent
2016-07-31 updated block diagram
2016-08-03 Updated README.md for V2 info
    First meaningful V2 update.
2016-08-08 current observation dataset
2016-08-14 Remove wemo directory
2016-08-14 init commit, copied from /home/pi/bin
2016-08-22 set RLOGPATH to /dev/null
2016-08-22 misc clean up
2016-08-23 updating README.md
2016-08-28 modified to use external modules in ./shared.js
2016-08-28 added back MIT License wording
2016-08-30 Update NOTICE,txt
2016-08-31 changed to Apache License
2016-09-03 ignore last newline after reading host and ip info in getPanelStatus()
2016-09-04 latest sensor database
2016-09-04 test database - no longer used
2016-09-04 init commit of V1 README.md
2016-09-04 updated LICENSE file
2016-09-04 added distinction between Apache and Amazon Licenses
2016-09-04 updated README.md links
2016-09-12 declared local var for all for loops
2016-09-12 local var declaration of i in for loop
2016-09-12 declared i as local var in for loop
2016-09-12 removed function calcRelT since its declared in shared
2016-09-12 removed function waitCLKchange since it wasn't used added some comments
2016-09-12 added explicit var declaration of for loop variables
2016-10-16 shortened delays in sendPolyInSession
2016-10-16 fixed typo in comment
2016-10-26 lengthened delays in sendPolyInSession
2016-12-18 findPlacesNotReady modified and used in place of zonesNotActive to fix motion sensors stopping arming
2016-12-19 fixes #30
2016-12-20 fixes #31
2016-12-25 fixes #32
2016-12-25 Fixes #16
2017-03-31 Update comments to reflect design of keybus data corruption mitigation, part of #35
2017-03-31 Update readme to reflect design of keybus data corruption mitigation, part of #35
2017-04-01 force lower case on ASR return values, part of #34
2019-07-20 updated .gitignore
2019-07-20 updated schematic and added pcb layout
2019-08-04 fixed pcb footprint for OSTTC020162
2019-08-05 added pcb photos
2019-09-08 updated paths after R upgrade and reinstall
2019-09-09 replace strncpy w/memcpy to avoid nul termination
2019-09-09 use short int for zone index to prevent overflow warn
2019-09-09 increase str size to prevent possible overflow
2019-09-09 changes to prevent possible truncation in popen() to R
2019-09-11 fix Rscript path
2019-09-11 fix bad panel reads after upgrade to 4.19.59-rt23-v7+
2019-09-11 update comments and whitespace
2019-09-11 added mkzip.sh
2019-09-12 set PTHREAD_EXPLICIT_SCHED to stop pthreads from inheriting pri from main
2019-09-13 change panel i/o wakeup interval to 100 us to lower mcps
2019-09-13 add conditional compile option for R logging
2019-09-14 add VERBOSE compile option
2019-09-14 log short panel word reads to stdout instead of stderr
2019-09-14 add TESTRT compiler option
2019-09-14 update comments
2019-09-15 add RLOG string preprocessor token
2019-09-15 added package-lock.json
2019-09-15 updated paths
2019-09-15 update paths and comments
2019-09-15 added scripts dir
2019-09-15 added kprw-server service config
2019-09-15 add real time test data
2020-12-18 comment out code to toggle lights

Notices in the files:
README.md:
Licensing:
The ALL project is almost completely licensed under the [Apache License 2.0](http://choosealicense.com/licenses/apache-2.0/) unless otherwise specified in a LICENSE.txt file in a source code directory. The only exception is the code in the file [trainInSession.js](https://github.com/goruck/all/blob/master/lambda/amzn/trainInSession.js) and related documentation in this README which are licensed under the [Amazon Software License](https://aws.amazon.com/asl/).
kgiu/kicad.kicad_pcb:
Copyright (c) 2019 Lindo St. Angel
